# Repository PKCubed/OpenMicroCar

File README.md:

# OpenMicroCar
An ESP32 based 4-motor vehicle designed as a single circuit board.

The idea here is to build 4 or more of these, and play a game of capture the flag with an analog FPV system on each little car. The IR leds and receivers will be used to "shoot" other cars laser-tag style. The ESP32s will use WiFi, or something else to communicate with a raspberry pi server. There will be two zones, one for each team, that are considered safe zones for that team, and will be another esp32 or esp8266 that has an IR receiver. When that receiver detects a car's infrared transmission, it knows it is in the safe zone. An opponent can drive into the safe zone of it's opposing team to capture its flag. It then has to get back to it's safe zone. If it is shot in the middle by the opponent, the flag is transferred to the car that shot it. They then have to bring it to their safe side. If a car gets shot, it must drive back to its safe zone before it can shoot or capture flags.

A car will be colored with its team color, orange or purple. When a car has a flag, the LEDs will blink in a fast pattern. When a car has been shot, its leds get dim and some leds fade red until it gets back to safety. When a car is shot, but is still in a safe zone, some leds will flash white and quickly fade back to the team color.

This tiny car has a PCB footprint of just 55 by 85.5 millimeters. The components all together cost under $30. It's designed to have 4 N20 motors soldered to the bottom, and held on by wrapping 2 lengths of wire around them and soldering to the PCB. Each motor has its own PWM control, as well as direction and braking control.

There are 12 infrared leds positioned around the car, all broadcasting the same signal from the ESP32 through a transistor. There are 2 IR receivers. One in the front designed to be the "shooting" receiver, and one in the back to alert the driver if they are being followed (may or may not get implemented).

There are also 12 WS2812b addressable RGB leds on each car. 8 facing down, and 4 facing up.

There is provision for a speaker and amplifier IC on board. This can be used to make beeps and boops, or maybe I'll try to output actual sampled sounds.

# Communication Details
Everything here is just my plans. Nothing has been actually tested and done yet.

Each car will be controlled through a web interface on people's phones. This web interface will come from a python program on a raspberry pi. When someone want's their car to go forward, they press the button on the web interface, which the python program sees, and then sends via wifi socket to the esp32 on that person's car, that they want to go forward. If the car doesn't hear from the python program for 1 second, it shuts off and goes to the disconnected failsafe state, that way it won't just drive away. We want the button latency to be as low as possible, approaching imperceptible.

Each car will send out a couple bytes through the IR leds that will let other cars know which car it is. This will be the car ID code.

People can also press the shoot button on their phone. This will tell the python program to request a shoot from the car. This will then read data through the IR receiver, and save any car ID codes it sees. It will report these back to python. At the same time, if the safe zone receivers see any IR car ID codes, Python will have seen that. If any of the shot cars match the safe cars, they will not be affected, but will be sent the safe shot signal to flash their LEDs and make a noise similar to that you get when you shoot a metal baloon in BTD Battles. If a car is not detected to be in a safe zone, it will be sent the shot signal, and it will be marked as shot until python sees it has been received by it's safe zone receiver.

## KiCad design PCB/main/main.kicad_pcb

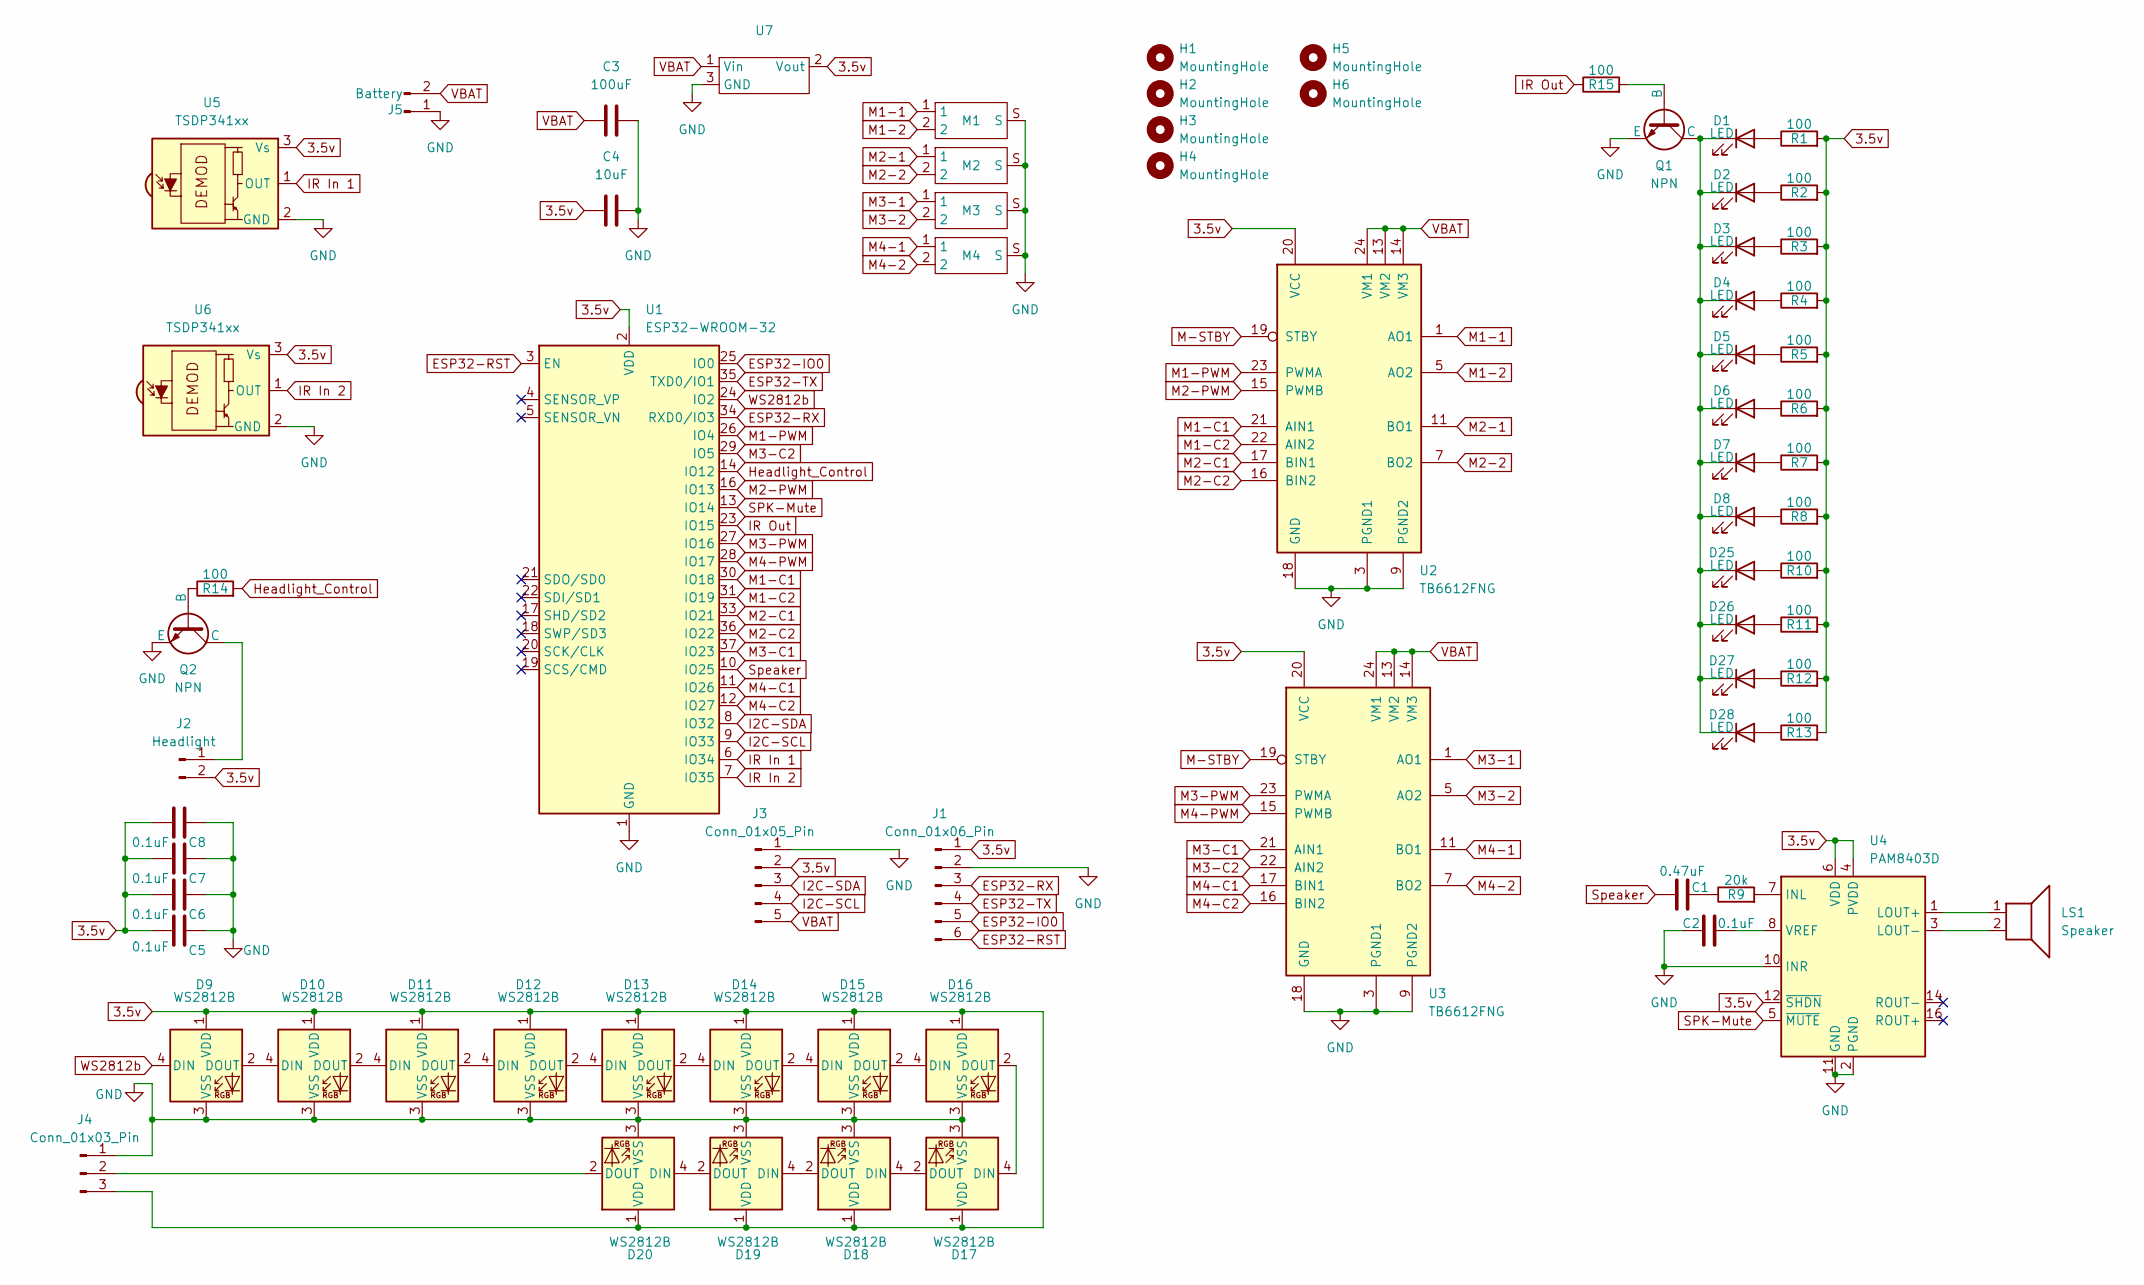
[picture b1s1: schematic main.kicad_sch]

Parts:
C1: 0.47uF; C_Disc_D5.0mm_W2.5mm_P2.50mm
C2: 0.1uF; C_Disc_D5.0mm_W2.5mm_P2.50mm
C3: 100uF; CP_Radial_D5.0mm_P2.00mm
C4: 10uF; CP_Radial_D5.0mm_P2.00mm
C5, C6, C7, C8: 0.1uF; C_0603_1608Metric_Pad1.08x0.95mm_HandSolder
D1, D3, D5, D7, D25: LED; Right Angle LED Reversed
D2, D4, D6, D8, D26, D27, D28: LED; Right Angle LED
D9, D10, D11, D12, D13, D14, D15, D16, D17, D18, D19, D20: WS2812B; LED_WS2812B_PLCC4_5.0x5.0mm_P3.2mm
H1, H2, H3, H4, H5, H6: MountingHole; MountingHole_3.2mm_M3
J1: Conn_01x06_Pin; PinHeader_1x06_P2.54mm_Vertical
J2: Headlight; PinHeader_1x02_P2.54mm_Vertical
J3: Conn_01x05_Pin; PinHeader_1x05_P2.54mm_Vertical
J4: Conn_01x03_Pin; PinHeader_1x03_P2.54mm_Vertical
J5: Battery; PinHeader_1x02_P2.54mm_Vertical
LS1: Speaker; PinHeader_1x02_P2.54mm_Vertical
M1, M2, M3, M4: N20 Motor
Q1, Q2: NPN; SOT-23-3
R1, R2, R3, R4, R5, R6, R7, R8, R10, R11, R12, R13: 100; R_Axial_DIN0204_L3.6mm_D1.6mm_P2.54mm_Vertical
R9: 20k; R_Axial_DIN0204_L3.6mm_D1.6mm_P2.54mm_Vertical
R14, R15: 100; R_0805_2012Metric_Pad1.20x1.40mm_HandSolder
U1: ESP32-WROOM-32
U2, U3: TB6612FNG; SSOP-24_5.3x8.2mm_P0.65mm
U4: PAM8403D; SOP-16_3.9x9.9mm_P1.27mm
U5, U6: TSDP341xx; Vishay_MINICAST-3Pin
U7: DC Buck Converter

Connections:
3.5v: C4.1, C5.2, C6.2, C7.2, C8.2, D9.1 (VDD), D10.1 (VDD), D11.1 (VDD), D12.1 (VDD), D13.1 (VDD), D14.1 (VDD), D15.1 (VDD), D16.1 (VDD), D17.1 (VDD), D18.1 (VDD), D19.1 (VDD), D20.1 (VDD), J1.1, J2.2, J3.2, J4.3, R1.2, R2.2, R3.2, R4.2, R5.2, R6.2, R7.2, R8.2, R10.2, R11.2, R12.2, R13.2, U1.2 (VDD), U2.20 (VCC), U3.20 (VCC), U4.4 (PVDD), U4.6 (VDD), U4.12 (~SHDN), U4.13 (PVDD), U5.3 (Vs), U6.3 (Vs), U7.2 (Vout)
ESP32-IO0: J1.5, U1.25 (IO0)
ESP32-RST: J1.6, U1.3 (EN)
ESP32-RX: J1.3, U1.34 (RXD0/IO3)
ESP32-TX: J1.4, U1.35 (TXD0/IO1)
GND: C2.1, C3.2, C4.2, C5.1, C6.1, C7.1, C8.1, D9.3 (VSS), D10.3 (VSS), D11.3 (VSS), D12.3 (VSS), D13.3 (VSS), D14.3 (VSS), D15.3 (VSS), D16.3 (VSS), D17.3 (VSS), D18.3 (VSS), D19.3 (VSS), D20.3 (VSS), J1.2, J3.1, J4.1, J5.1, M1.S, M2.S, M3.S, M4.S, Q1.3 (E), Q2.3 (E), U1.1 (GND), U1.15 (GND), U1.38 (GND), U1.39 (GND), U2.3 (PGND1), U2.4 (PGND1), U2.9 (PGND2), U2.10 (PGND2), U2.18 (GND), U3.3 (PGND1), U3.4 (PGND1), U3.9 (PGND2), U3.10 (PGND2), U3.18 (GND), U4.2 (PGND), U4.10 (INR), U4.11 (GND), U4.15 (PGND), U5.2 (GND), U6.2 (GND), U7.3 (GND)
Headlight_Control: R14.2, U1.14 (IO12)
I2C-SCL: J3.4, U1.9 (IO33)
I2C-SDA: J3.3, U1.8 (IO32)
IR In 1: U1.6 (IO34), U5.1 (OUT)
IR In 2: U1.7 (IO35), U6.1 (OUT)
IR Out: R15.1, U1.23 (IO15)
M1-1: M1.1, U2.1 (AO1), U2.2 (AO1)
M1-2: M1.2, U2.5 (AO2), U2.6 (AO2)
M1-C1: U1.30 (IO18), U2.21 (AIN1)
M1-C2: U1.31 (IO19), U2.22 (AIN2)
M1-PWM: U1.26 (IO4), U2.23 (PWMA)
M2-1: M2.1, U2.11 (BO1), U2.12 (BO1)
M2-2: M2.2, U2.7 (BO2), U2.8 (BO2)
M2-C1: U1.33 (IO21), U2.17 (BIN1)
M2-C2: U1.36 (IO22), U2.16 (BIN2)
M2-PWM: U1.16 (IO13), U2.15 (PWMB)
M3-1: M3.1, U3.1 (AO1), U3.2 (AO1)
M3-2: M3.2, U3.5 (AO2), U3.6 (AO2)
M3-C1: U1.37 (IO23), U3.21 (AIN1)
M3-C2: U1.29 (IO5), U3.22 (AIN2)
M3-PWM: U1.27 (IO16), U3.23 (PWMA)
M4-1: M4.1, U3.11 (BO1), U3.12 (BO1)
M4-2: M4.2, U3.7 (BO2), U3.8 (BO2)
M4-C1: U1.11 (IO26), U3.17 (BIN1)
M4-C2: U1.12 (IO27), U3.16 (BIN2)
M4-PWM: U1.28 (IO17), U3.15 (PWMB)
M-STBY: U2.19 (STBY), U3.19 (STBY)
unnamed: C1.2, R9.1
unnamed: D1.2 (A), R1.1
unnamed: D1.1 (K), D2.1 (K), D3.1 (K), D4.1 (K), D5.1 (K), D6.1 (K), D7.1 (K), D8.1 (K), D25.1 (K), D26.1 (K), D27.1 (K), D28.1 (K), Q1.1 (C)
unnamed: D2.2 (A), R2.1
unnamed: D3.2 (A), R3.1
unnamed: D4.2 (A), R4.1
unnamed: D5.2 (A), R5.1
unnamed: D6.2 (A), R6.1
unnamed: D7.2 (A), R7.1
unnamed: D8.2 (A), R8.1
unnamed: D9.2 (DOUT), D10.4 (DIN)
unnamed: D10.2 (DOUT), D11.4 (DIN)
unnamed: D11.2 (DOUT), D12.4 (DIN)
unnamed: D12.2 (DOUT), D13.4 (DIN)
unnamed: D13.2 (DOUT), D14.4 (DIN)
unnamed: D14.2 (DOUT), D15.4 (DIN)
unnamed: D15.2 (DOUT), D16.4 (DIN)
unnamed: D16.2 (DOUT), D17.4 (DIN)
unnamed: D17.2 (DOUT), D18.4 (DIN)
unnamed: D18.2 (DOUT), D19.4 (DIN)
unnamed: D19.2 (DOUT), D20.4 (DIN)
unnamed: D20.2 (DOUT), J4.2
unnamed: D25.2 (A), R10.1
unnamed: D26.2 (A), R11.1
unnamed: D27.2 (A), R12.1
unnamed: D28.2 (A), R13.1
unnamed: J2.1, Q2.1 (C)
unnamed: Q1.2 (B), R15.2
unnamed: Q2.2 (B), R14.1
unnamed: R9.2, U4.7 (INL)
unnamed: LS1.1, U4.1 (LOUT+)
unnamed: LS1.2, U4.3 (LOUT-)
unnamed: C2.2, U4.8 (VREF)
SPK-Mute: U1.13 (IO14), U4.5 (~MUTE)
Speaker: C1.1, U1.10 (IO25)
VBAT: C3.1, J3.5, J5.2, U2.13 (VM2), U2.14 (VM3), U2.24 (VM1), U3.13 (VM2), U3.14 (VM3), U3.24 (VM1), U7.1 (Vin)
WS2812b: D9.4 (DIN), U1.24 (IO2)

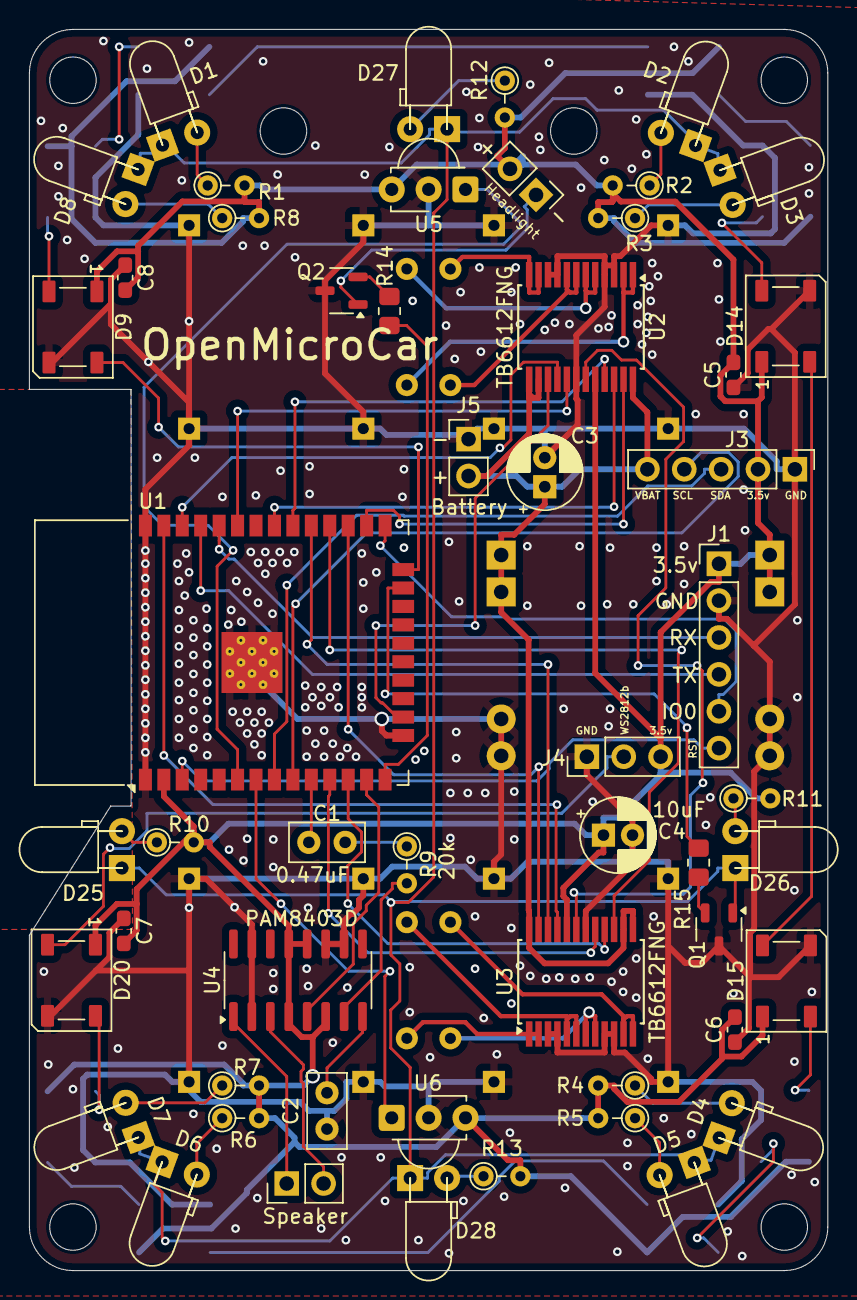
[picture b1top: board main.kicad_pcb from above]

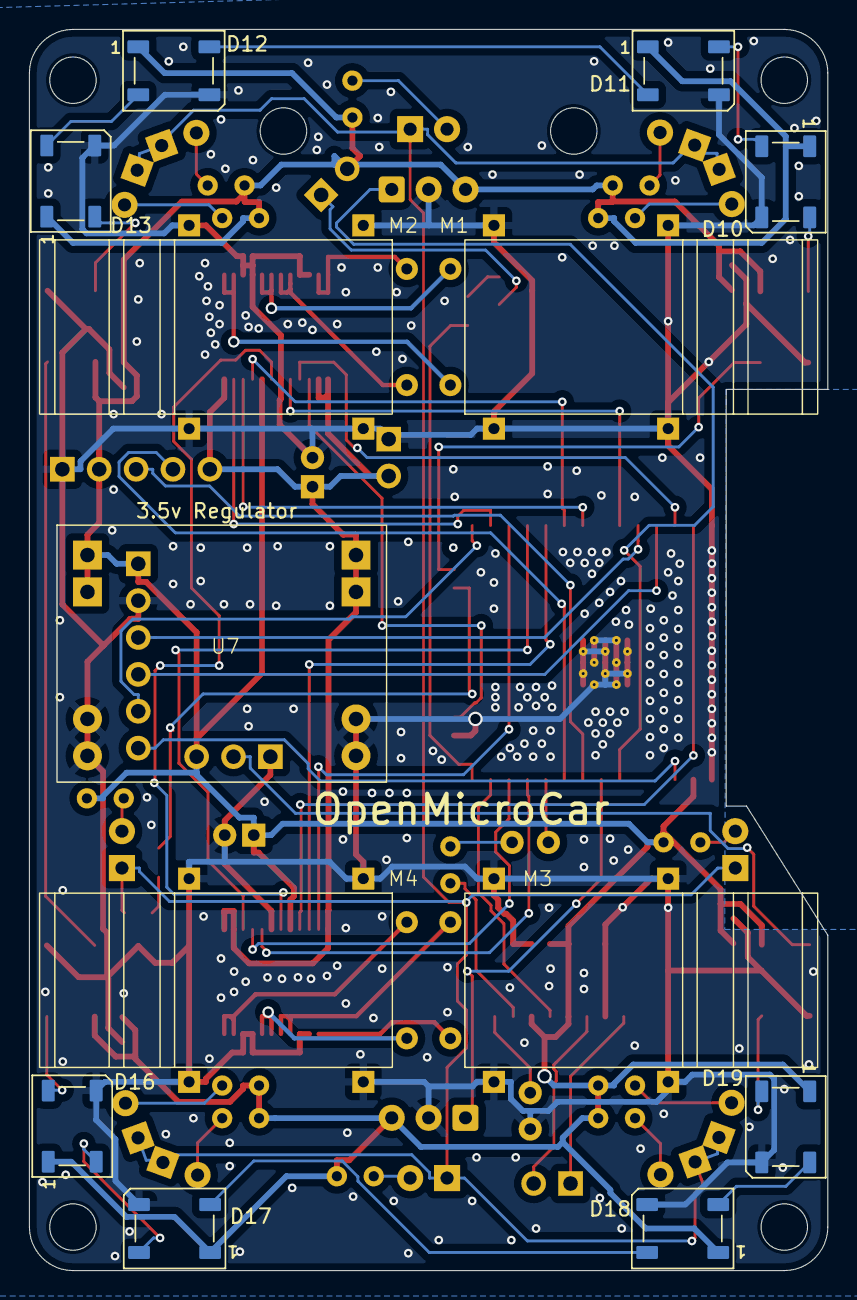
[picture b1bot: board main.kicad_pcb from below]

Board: 2 copper layers, 55.0 x 85.5 mm, 72 parts (13 on the bottom side), 70 nets.

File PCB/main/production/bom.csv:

Designator,Footprint,Quantity,Value,LCSC Part #
C1,C_Disc_D5.0mm_W2.5mm_P2.50mm,1,0.47uF,
C2,C_Disc_D5.0mm_W2.5mm_P2.50mm,1,0.1uF,
C3,CP_Radial_D5.0mm_P2.00mm,1,100uF,
C4,CP_Radial_D5.0mm_P2.00mm,1,10uF,
"C5, C6, C7, C8",0603,4,0.1uF,
"D1, D25, D3, D5, D7",Right Angle LED Reversed,5,LED,
"D10, D11, D12, D13, D14, D15, D16, D17, D18, D19, D20, D9",LED_WS2812B_PLCC4_5.0x5.0mm_P3.2mm,12,WS2812B,
"D2, D26, D27, D28, D4, D6, D8",Right Angle LED,7,LED,
J1,PinHeader_1x06_P2.54mm_Vertical,1,Conn_01x06_Pin,
J2,PinHeader_1x02_P2.54mm_Vertical,1,Headlight,
J3,PinHeader_1x05_P2.54mm_Vertical,1,Conn_01x05_Pin,
J4,PinHeader_1x03_P2.54mm_Vertical,1,Conn_01x03_Pin,
J5,PinHeader_1x02_P2.54mm_Vertical,1,Battery,
LS1,PinHeader_1x02_P2.54mm_Vertical,1,Speaker,
"M1, M2, M3, M4",N20 Motor,4,~,
"Q1, Q2",SOT-23-3,2,NPN,
"R1, R10, R11, R12, R13, R2, R3, R4, R5, R6, R7, R8",R_Axial_DIN0204_L3.6mm_D1.6mm_P2.54mm_Vertical,12,100,
R9,R_Axial_DIN0204_L3.6mm_D1.6mm_P2.54mm_Vertical,1,20k,
U1,ESP32-WROOM-32,1,ESP32-WROOM-32,
"U2, U3",SSOP-24_5.3x8.2mm_P0.65mm,2,TB6612FNG,
U4,SOP-16_3.9x9.9mm_P1.27mm,1,PAM8403D,
"U5, U6",Vishay_MINICAST-3Pin,2,TSDP341xx,
U7,DC Buck Converter,1,~,

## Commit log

2025-08-03 Uploaded PCB Files
    This is the first version of the PCB I designed yesterday.
2025-08-03 Base Resistors and README.md
    Added base resistors to the headlight and IR led transistors (facepalm), and added to the main README.md.
2025-08-04 Initial Code
    Initial Coding. Waiting for PCBs to arrive for more development.
2025-08-27 added basic motor test
